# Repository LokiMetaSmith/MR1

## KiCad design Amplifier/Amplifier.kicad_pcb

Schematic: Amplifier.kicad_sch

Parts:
C1: 2pF; C_0402_1005Metric; LCSC C161316
C3: 15pF; C_0402_1005Metric; LCSC C33148
C6, C9, C14, C20: 100nF; C_0402_1005Metric; LCSC C49678
C7, C8: 10nF; C_0402_1005Metric; LCSC C1525
C10, C12, C19, C31, C32, C33, C34, C39: 100nF; C_0402_1005Metric; LCSC C15255
C11: 4.7u; C_0402_1005Metric; Manufacturer_Part_Number JMK107C6475KA-T; LCSC C19702
C29, C30: 10pF; C_0402_1005Metric; LCSC C1548
C35: 10u; C_0402_1005Metric; MPN GRM21BR61H106KE43K; LCSC C1713
C40, C42: 100nF; C_0402_1005Metric; Mouser PN 710-885012205037; LCSC C15255
C41: 1nF; C_0402_1005Metric; LCSC C1523
D82: MBR0540; D_SOD-123; MPN MBR0540L-TP; LCSC C5204747
FB1, FB2: HZ0402A152R-10; L_0402_1005Metric; LCSC C442654
J7: Conn_01x14_MountingPin; XUNPU_FPC-05F-14PH15_1x14_P0.5mm_Horizontal; LCSC C2856818
NT3, NT4, NT6, NT7, NT8, NT9: NetTie_2; NetTie-2_SMD_Pad0.5mm
P1, P3, P4, P6, P7, P8, P9, P10, P11, P12: PogoPin_MillMax_SMT_1Pin
P2, P5: PogoPin_MillMax_SMT_1Pin_Guarded; PogoPin_SMT_Circle_Guard_Notched
Q3: 2N7002; SOT-23; LCSC C8545
R1: 1G; R_0402_1005Metric; LCSC HVC0805T1007JET
R3, R5: 1K; R_0402_1005Metric; LCSC C17513
R4: 100; R_0402_1005Metric; LCSC C25097
R6: 1K; R_0402_1005Metric; LCSC C25149
R8: 100; R_0402_1005Metric; LCSC C17408
R10, R14, R15: 100k; R_0402_1005Metric; LCSC C60491
R16: 1M; R_0402_1005Metric; LCSC C25488
R27, R41: 27; R_0402_1005Metric; MPN RC0402JR-0727RL; LCSC C25078
R28, R29, R30, R31, R32, R33: 49.9; R_0402_1005Metric; MPN RC0402JR-0727RL; LCSC C4074199
R43, R44, R45, R46: 499 (0.1%); R_0402_1005Metric; LCSC C25132
SYM1: SYM_Arrow45_Large; Fluid_Overlay_SILKSCREEN_ONLY
U2: LMP7721; SOIC-8_3.9x4.9mm_P1.27mm; Mouser PN 926-LMP7721MA/NOPB
U5: OPA2192IDR; SOIC-8_3.9x4.9mm_P1.27mm; MPN OPA2192IDR; LCSC C110074
U6: ADA4940-1xCP; LFCSP-16-1EP_3x3mm_P0.5mm_EP1.3x1.3mm_ThermalVias; MPN ADA4940-1ACPZ-RL; LCSC C529241
U13: AD40xxBRMZ; MSOP-10_3x3mm_P0.5mm; MPN AD4011BCPZ-RL7; LCSC C539308
U14: LP5907MFX-1.8; SOT-23-5; MPN LP5907MFX-1.8/NOPB; LCSC C92498
U16: LTC6268xS8; SO-8_3.9x4.9mm_P1.27mm; MPN LTC6268IS8#TRPBF; LCSC C689169
U17: ADG1219BRMZ; MSOP-8_3x3mm_P0.65mm; MPN ADG1219BRMZ; LCSC C206796

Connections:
+1V8: C11.1, U13.2 (VDD), U14.5 (OUT)
+3.3VA: C33.1, FB1.2, FB2.1, R14.1, U13.10 (VIO), U17.1 (EN)
+3V3: FB1.1, J7.1
/>PORE_AMP: J7.14, P9.1 (PIN_1)
/CE_GNDA: NT8.1, P7.1 (PIN_1)
/GDAC_CLK: R31.1, U13.8 (SCK)
/GDAC_EN: R29.1, U13.6 (CNV)
/GDAC_SDI: R30.1, U13.9 (SDI)
/GDAC_SDO: R28.1, U13.7 (SDO)
/GNDA_SHLD: NT9.2, P1.1 (PIN_1)
/GNDA_WEEP: D82.2 (A), NT6.1, P12.1 (PIN_1), Q3.2 (S)
/GUARD: NT3.1, P4.1 (PIN_1), P5.2 (GUARD), P6.1 (PIN_1), U2.2 (NC), U2.7 (NC)
/GUARD_WIDE: P2.2 (GUARD), P3.1 (PIN_1), U5.6 (-), U5.7
/RE_TRANS: P8.1 (PIN_1), R6.2
/ROUTE_SEL: R33.1, U17.8 (IN)
/R_WEEP_GATE: D82.1 (K), R15.2, R16.1
/R_WEEP_PULL: Q3.3 (D), R14.2, U14.3 (EN)
/Route1_OUT: C9.1, R3.1, U16.6, U17.7 (SA)
/Route2_OUT: R32.2, U17.5 (SB)
/SHIELD: NT4.1, NT7.2
/SHIELD_AMP: J7.MP (MountPin), NT4.2, NT9.1
/Signal_Return: R45.1, U17.6 (D)
/Vbias: C6.1, C14.1, C35.1, NT3.2, R4.1, R6.1, U2.1 (+), U5.3 (+), U5.5 (+), U13.1 (REF), U16.1 (NC), U16.4 (NC)
/Virtual_Ground: C9.2, R3.2, R4.2, U16.2 (-)
/WEEP_SENSE: P11.1 (PIN_1), R15.1
/WS_CIS: C1.2, P5.1 (SIG), R1.2, U2.8 (-)
/WS_CIS_WIDE: C3.2, P2.1 (SIG), R10.2, U5.2 (-)
GND: J7.2, J7.8
GNDA: C6.2, C7.2, C8.2, C10.2, C11.2, C12.2, C14.2, C19.2, C20.2, C29.1, C30.2, C31.2, C32.2, C33.2, C34.2, C35.2, C39.2, C40.2, C42.2, J7.9, J7.11, J7.13, NT6.2, NT8.2, P10.1 (PIN_1), R5.2, R43.1, U6.9 (VOCM), U6.17 (EP), U13.5 (GND), U14.2 (GND), U17.3 (GND)
unnamed: C1.1, R1.1, R8.2, U2.4
unnamed: C39.1, NT7.1
unnamed: J7.3, R31.2
unnamed: J7.4, R33.2
unnamed: J7.5, R28.2
unnamed: J7.6, R29.2
unnamed: J7.7, R30.2
unnamed: Q3.1 (G), R16.2
unnamed: C3.1, R10.1, R32.1, U5.1
unnamed: R44.2, U6.4 (+FB)
unnamed: R45.2, R46.2, U6.2 (+IN)
unnamed: R27.1, U6.10 (+OUT)
unnamed: R46.1, U6.1 (-FB)
unnamed: R43.2, R44.1, U6.3 (-IN)
unnamed: R41.1, U6.11 (-OUT)
unnamed: C29.2, C41.1, R27.2, U13.3 (IN+)
unnamed: C30.1, C41.2, R41.2, U13.4 (IN-)
unnamed: C34.1, FB2.2, U14.1 (IN)
unnamed: R5.1, R8.1, U16.3 (+)
VDDA: C7.1, C10.1, C19.1, C31.1, C40.1, J7.10, U2.6 (V+), U5.8 (V+), U6.5 (+Vs), U6.6 (+Vs), U6.7 (+Vs), U6.8 (+Vs), U16.7 (V+), U17.2 (VDD)
VSSA: C8.1, C12.1, C20.1, C32.1, C42.1, J7.12, U2.3 (V-), U5.4 (V-), U6.13 (-Vs), U6.14 (-Vs), U6.15 (-Vs), U6.16 (-Vs), U16.5 (V-), U17.4 (VSS)

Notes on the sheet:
SM10B-SRSS-TB
3. Selecting the Precision ADC To capture <1µV signals, you need a 24-bit or 32-bit Delta-Sigma ADC. The standard 12-bit or 16-bit SAR ADCs used in microcontrollers will not see the signal floor you have created. Top Recommendations: TI ADS1261 (24-bit / 32-bit mode): Why: It has a built-in PGA (Pr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
Ceramic capacitors are piezoelectric – mechanical vibrations and noises will create charge across the capacitor. Be careful when using ceramic caps in the input, integration, feedback or biasing networks.
LTC6268
consider cat 7 flat ribbon cable, 8 pairs, shielded
low noise voltage converters
Stage 2 Voltage Amplifier
R1 1206
Stage 1: Transimpedance Amp
Stability in ultra-low noise regulators is dictated by the **Output Capacitance ()** and the **Noise Reduction Capacitance ()**. If these ratios are wrong, the LDO will oscillate, turning your "clean" power supply into a radio transmitter. ### 1. The LDO Component Values (The Critical Stage) These 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
https://www.vpi.us/bulk-cable-sf/super-flat-cat7-736#idTab9
R_DAMP
MG Chemicals 422C conformal coating
amplifier board
RF-damping capacitor
For high-speed nanopore sensing, the answer is definitive: **Do NOT tie them together.** You should use **Separate Voltage References** (or at least strictly buffered separate paths) for your ADC and your Bias Driver. Here is the engineering reality of why sharing a "Reference Rail" will introduce 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
No, the schematic recipe I provided above is **Fixed Gain (10x)**. It uses a standard resistor, so the zoom level is locked. Since you are removing the MAX9939 (which *was* a variable gain amplifier), you likely want to keep that functionality—especially since Nanopores vary wildly in current. A 1 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
PTFE (ZYF255DA): Dk .approx 2.55
499Ω Metal Film Resistor
we need to play back a waveform
250ft 32AWG CAT7 STP Solid, 0.075" Super Flat Bulk Ethernet Bare Copper Cable - White.
Using an **Optically Isolated Current Source (LED + Photodiode)** is the "Ferrari" of dummy loads for nanopore amplifiers. While the resistor method (like in the EarlGrey PDF) is great for checking baseline noise, the LED/Photodiode method is superior for checking **bandwidth** and **step response*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
pins for holding the board in place while applying adhesive https://www.mcmaster.com/98378A208/
SSH-003T-P0.2-H #32 to #28 (0.032 to 0.081) 0.4 to 0.8 23,000
SHR-10V-S
C2 and C3 X5R

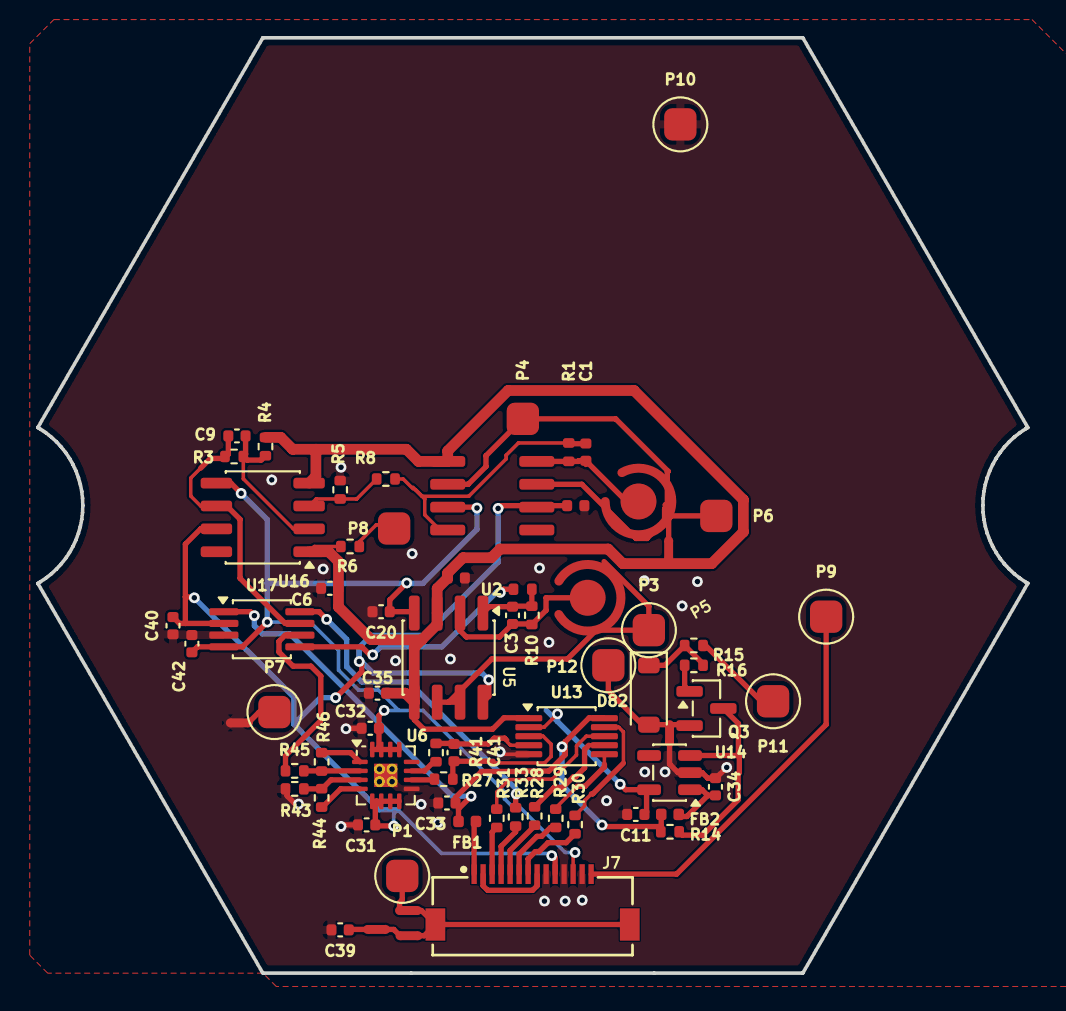
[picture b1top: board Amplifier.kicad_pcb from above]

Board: 2 copper layers, 55.0 x 52.0 mm, 70 parts (1 on the bottom side), 50 nets.

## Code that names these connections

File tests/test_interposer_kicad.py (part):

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            self.assertIn(f'(symbol "{s}"', sym_txt, f"Symbol {s} must be defined in Interposer.kicad_sym")

        # Validate pin names in PogoPin_Target_12Pin_Distributed
        for pin_name in ["GNDA_SHLD", "WS_CIS_WIDE", "GUARD_WIDE", "GUARD_CIS_A", "WS_CIS", "GUARD_CIS_B", "CE_GNDA", "RE_TRANS", ">PORE_AMP", "GNDA", "WEEP_SENSE", "GNDA_WEEP"]:
            self.assertIn(f'(name "{pin_name}"', sym_txt, f"Pin {pin_name} must be in PogoPin_Target_12Pin_Distributed")

        table_txt = table_file.read_text(encoding="utf-8")
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            nets[m.group(1)] = re.findall(r'\(node\s+\(ref\s+\"([^\"]+)\"\)\s+\(pin\s+\"([^\"]+)\"\)', m.group(0))

        # Route 1: Passive quiet guard for LMP7721 via NT3
        self.assertIn('(label "GUARD"', sch_txt)
        self.assertIn(('NT3', '1'), nets.get('/GUARD', []), "NT3 Pin 1 must connect directly to GUARD net for LMP7721")
        self.assertIn(('NT3', '2'), nets.get('/Vbias', []), "NT3 Pin 2 must connect to Vbias")
        # Route 2: Active guard buffer for GUARD_WIDE using OPA2192 Unit 2
        self.assertIn('(label "GUARD_WIDE"', sch_txt)
        self.assertNotIn('"NT6"', sch_txt, "NT6 must be removed so active GUARD_WIDE is not shorted to Vbias")
        # U16 LTC6268 Gain Stage: R3 feedback restored, R4 tied to Vbias
        self.assertIn(('R3', '1'), nets.get('/Route1_OUT', []), "R3 feedback loop must connect to U16 output (Route1_OUT)")
        self.assertIn(('R3', '2'), nets.get('/Virtual_Ground', []), "R3 pin 2 must connect to Virtual_Ground")
        self.assertIn(('R4', '1'), nets.get('/Vbias', []), "R4 must connect to Vbias")

    def test_amplifier_route2_adg1219_multiplexer_integration(self):
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        # Verify U17 drain connects to Signal_Return (driving R45 differential ADC driver input)
        d_net = [n for n, nodes in nets.items() if ('U17', '6') in nodes]
        self.assertEqual(len(d_net), 1, "U17 pin 6 (D) must belong to exactly one net")
        self.assertEqual(d_net[0], "/Signal_Return", "U17 Drain (pin 6) must connect to Signal_Return")
        self.assertIn(('R45', '1'), nets[d_net[0]], "Signal_Return must feed R45 ADC driver resistor")
        # Ensure U16 (Route 1) and U5 (Route 2) do NOT connect directly to Signal_Return
        self.assertNotIn(('U16', '6'), nets[d_net[0]], "U16.6 must NOT short directly to Signal_Return")
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
        # Verify summing node WS_CIS_WIDE
        wide_net = nets.get("/WS_CIS_WIDE", [])
        self.assertIn(('U5', '2'), wide_net, "U5 pin 2 (-IN) must connect to WS_CIS_WIDE")
        self.assertIn(('R10', '2'), wide_net, "R10 pin 2 must connect to WS_CIS_WIDE")
        self.assertIn(('C3', '2'), wide_net, "C3 pin 2 must connect to WS_CIS_WIDE")
        self.assertIn(('P2', '1'), wide_net, "P2 Pin 1 (WS_CIS_WIDE SMT pin) must connect to WS_CIS_WIDE")

        # Verify control line ROUTE_SEL
        route_net = nets.get("/ROUTE_SEL", [])
        self.assertIn(('U17', '8'), route_net, "U17 IN (pin 8) must connect to /ROUTE_SEL")

        # Verify enable line
        p3v3_net = nets.get("+3V3", [])
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
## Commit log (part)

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2026-01-08 Update Cartridge to Hexagonal Single-Sided PCB stack
    - Updated `PCB_Rigid_Active` to be a full 60mm Hexagonal Plate ("Single-Sided PCBA") with 4 bottom-side electrodes and Top Fluid pass-throughs.
    - Removed `Carrier_Frame_Hex` entirely; the PCB now stacks directly between gaskets.
    - Modified `Gasket_Low_Dead_Volume` to split the bottom layer into Center (Chip) and Trans Loop zones.
    - Implemented "U-Turn" Trans fluid routing in `Plate_1_Base_Hex_3D`:
    - Blind Vias (no bottom puncture) connect Inlet -> Channel -> Up to Pads -> Down to Center.
    - Implemented "Sloped Roof" (Rising Floor) channel geometry under the chip to prevent bubble trapping.
2026-02-01 Update Gasket_Low_Dead_Volume liquid ports to 4mm and deepen cable slot
    - Increased `port_d_laser` from 2.0mm to 4.0mm to match the liquid port size of the rigid plates.
    - Replaced the standard `Cable_Slot_2D` with a custom 12x12mm cutout centered at Y=-25 in `Gasket_Low_Dead_Volume`. This ensures the cable slot cuts deeper into the gasket body (to Y=-19mm) and fully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
    - Updated comments to reflect the new dimensions.
2026-02-19 Fix Housing_Pump_Lid export crash and update mating geometry
    - Replaced complex `threaded_rod` with simple cylinders in `Housing_Pump_Case` to resolve CGAL errors and timeout.
    - Replaced circular O-ring groove sweep with square profile in `Housing_Pump_Lid` to prevent WASM crash.
    - Updated `Housing_Pump_Lid` top feet recesses from trapezoids to 13.5mm cylinders to mate with Reader Case.
    - Increased `Housing_Pump_Lid` bottom indexing lip height to 5mm for better engagement.
2026-02-20 Revert simplifications and fix Pump Lid feet orientation
    - Reverted `Housing_Pump_Case` fluid ports to use `threaded_rod` (previously simplified to cylinders).
    - Reverted `Housing_Pump_Lid` O-ring groove to use `circle` profile (previously simplified to square).
    - Updated `Housing_Pump_Lid` feet recesses to use a tapered `trapezoid` shape (via `linear_extrude(scale=0.8)`) so the recess is wider at the top and narrower at the bottom, matching the mating feet 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
    - Verified that `npm run export` completes successfully (albeit slower) with these complex geometries restored.

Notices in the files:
tests/test_interposer_kicad.py:
Dedicated to the public domain under CC0 1.0 Universal (CC0-1.0).
SPDX-License-Identifier: CC0-1.0
